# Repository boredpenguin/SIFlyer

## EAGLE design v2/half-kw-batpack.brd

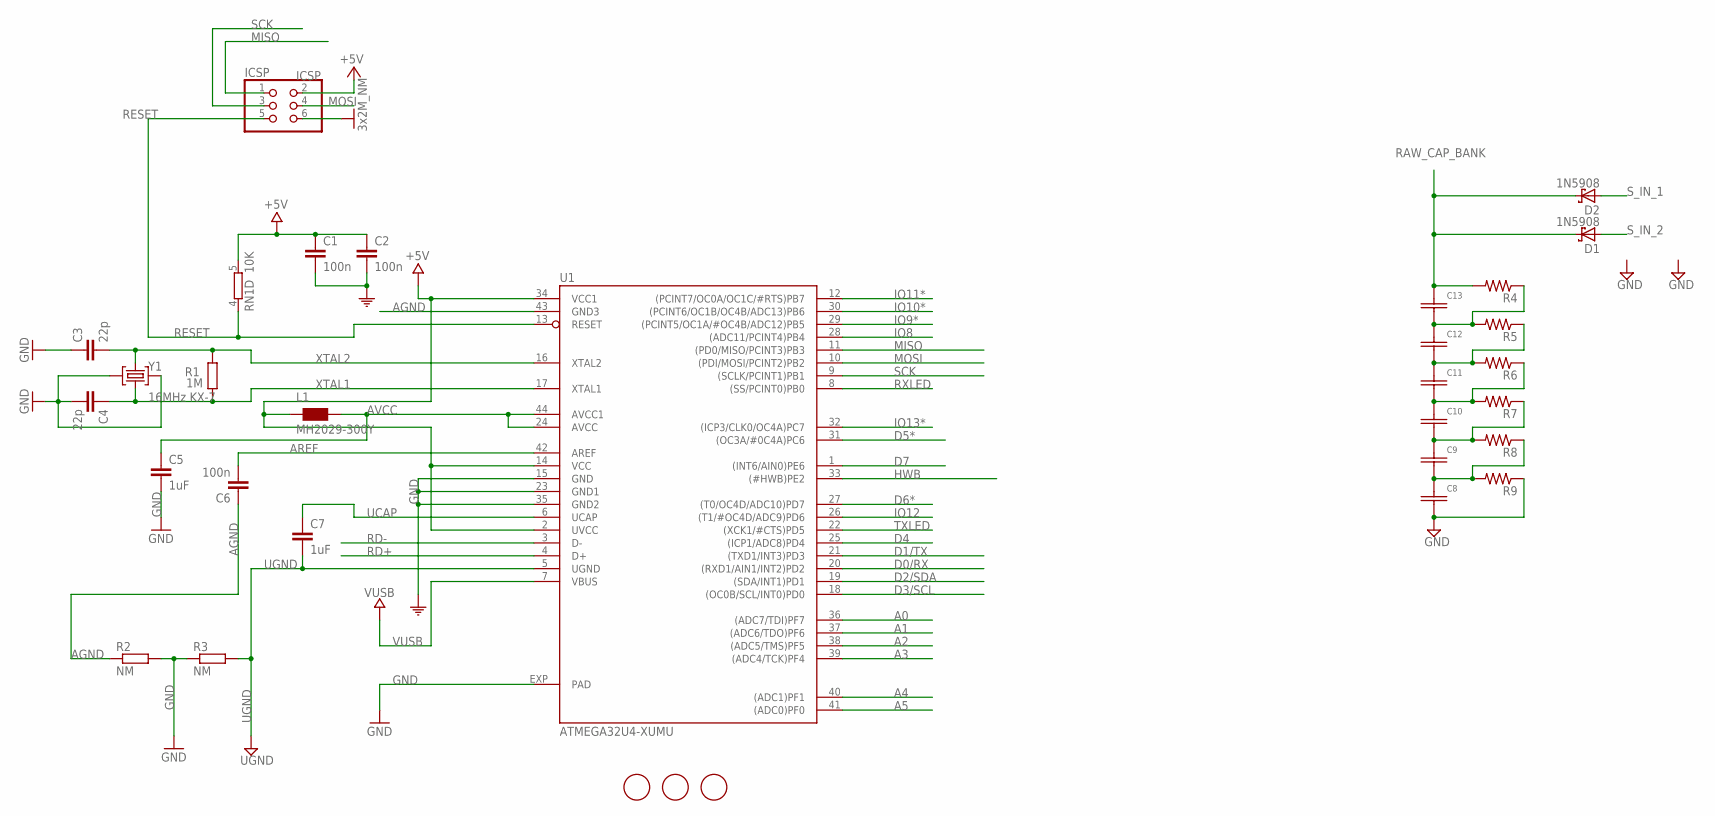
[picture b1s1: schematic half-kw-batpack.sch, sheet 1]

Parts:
C1, C2, C6: 100n; C0603-ROUND
C3, C4: 22p; C0603-ROUND
C5, C7: 1uF; C0603-ROUND
C8, C9, C10, C11, C12, C13: BCAP0100; MAXWELLBCAP100
D1, D2: 1N5908; C4111-15
FID1, FID2, FID3: FIDUCIALMOUNT; FIDUCIA-MOUNT
ICSP: ICSP; 2X03
L1: MH2029-300Y; 0805
R1: 1M; R0603-ROUND
R2, R3: NM; R0402
R4, R5, R6, R7, R8, R9: R-US_R1206; R1206
RN1: 10K; CAY16
U1: ATMEGA32U4-XUMU; QFN44ML7X7
Y1: 16MHz KX-7; CRYSTAL-3.2-2.5

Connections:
+5V: C1.1, C2.1, ICSP.2, L1.1, RN1.5 (2), U1.2 (UVCC), U1.14 (VCC), U1.34 (VCC1)
A0: U1.36 ((ADC7/TDI)PF7)
A1: U1.37 ((ADC6/TDO)PF6)
A2: U1.38 ((ADC5/TMS)PF5)
A3: U1.39 ((ADC4/TCK)PF4)
A4: U1.40 ((ADC1)PF1)
A5: U1.41 ((ADC0)PF0)
AGND: C6.1, R2.1, U1.43 (GND3)
AREF: C6.2, U1.42 (AREF)
AVCC: C5.1, L1.2, U1.24 (AVCC), U1.44 (AVCC1)
D0/RX: U1.20 ((RXD1/AIN1/INT2)PD2)
D1/TX: U1.21 ((TXD1/INT3)PD3)
D2/SDA: U1.19 ((SDA/INT1)PD1)
D3/SCL: U1.18 ((OC0B/SCL/INT0)PD0)
D4: U1.25 ((ICP1/ADC8)PD4)
D5*: U1.31 ((OC3A/#0C4A)PC6)
D6*: U1.27 ((T0/OC4D/ADC10)PD7)
D7: U1.1 ((INT6/AIN0)PE6)
GND: C1.2, C2.2, C3.1, C4.2, C5.2, C8.P$2, ICSP.6, R2.2, R3.1, R9.1, U1.15 (GND), U1.23 (GND1), U1.35 (GND2), U1.EXP (PAD), Y1.2 (GND), Y1.4 (GND)
HWB: U1.33 ((#HWB)PE2)
IO8: U1.28 ((ADC11/PCINT4)PB4)
IO9*: U1.29 ((PCINT5/OC1A/#OC4B/ADC12)PB5)
IO10*: U1.30 ((PCINT6/OC1B/OC4B/ADC13)PB6)
IO11*: U1.12 ((PCINT7/OC0A/OC1C/#RTS)PB7)
IO12: U1.26 ((T1/#OC4D/ADC9)PD6)
IO13*: U1.32 ((ICP3/CLK0/OC4A)PC7)
MISO: ICSP.1, U1.11 ((PD0/MISO/PCINT3)PB3)
MOSI: ICSP.4, U1.10 ((PDI/MOSI/PCINT2)PB2)
unnamed: C9.P$1, C10.P$2, R7.1, R8.2
unnamed: C10.P$1, C11.P$2, R6.1, R7.2
unnamed: C12.P$1, C13.P$2, R4.1, R5.2
unnamed: C11.P$1, C12.P$2, R5.1, R6.2
unnamed: C8.P$1, C9.P$2, R8.1, R9.2
RAW_CAP_BANK: C13.P$1, D1.C, D2.C, R4.2
RD+: U1.4 (D+)
RD-: U1.3 (D-)
RESET: ICSP.5, RN1.4 (1), U1.13 (RESET)
RXLED: U1.8 ((SS/PCINT0)PB0)
SCK: ICSP.3, U1.9 ((SCLK/PCINT1)PB1)
S_IN_1: D2.A
S_IN_2: D1.A
TXLED: U1.22 ((XCK1/#CTS)PD5)
UCAP: C7.1, U1.6 (UCAP)
UGND: C7.2, R3.2, U1.5 (UGND)
VUSB: U1.7 (VBUS)
XTAL1: C4.1, R1.1, U1.17 (XTAL1), Y1.1 (C1)
XTAL2: C3.2, R1.2, U1.16 (XTAL2), Y1.3 (C2)

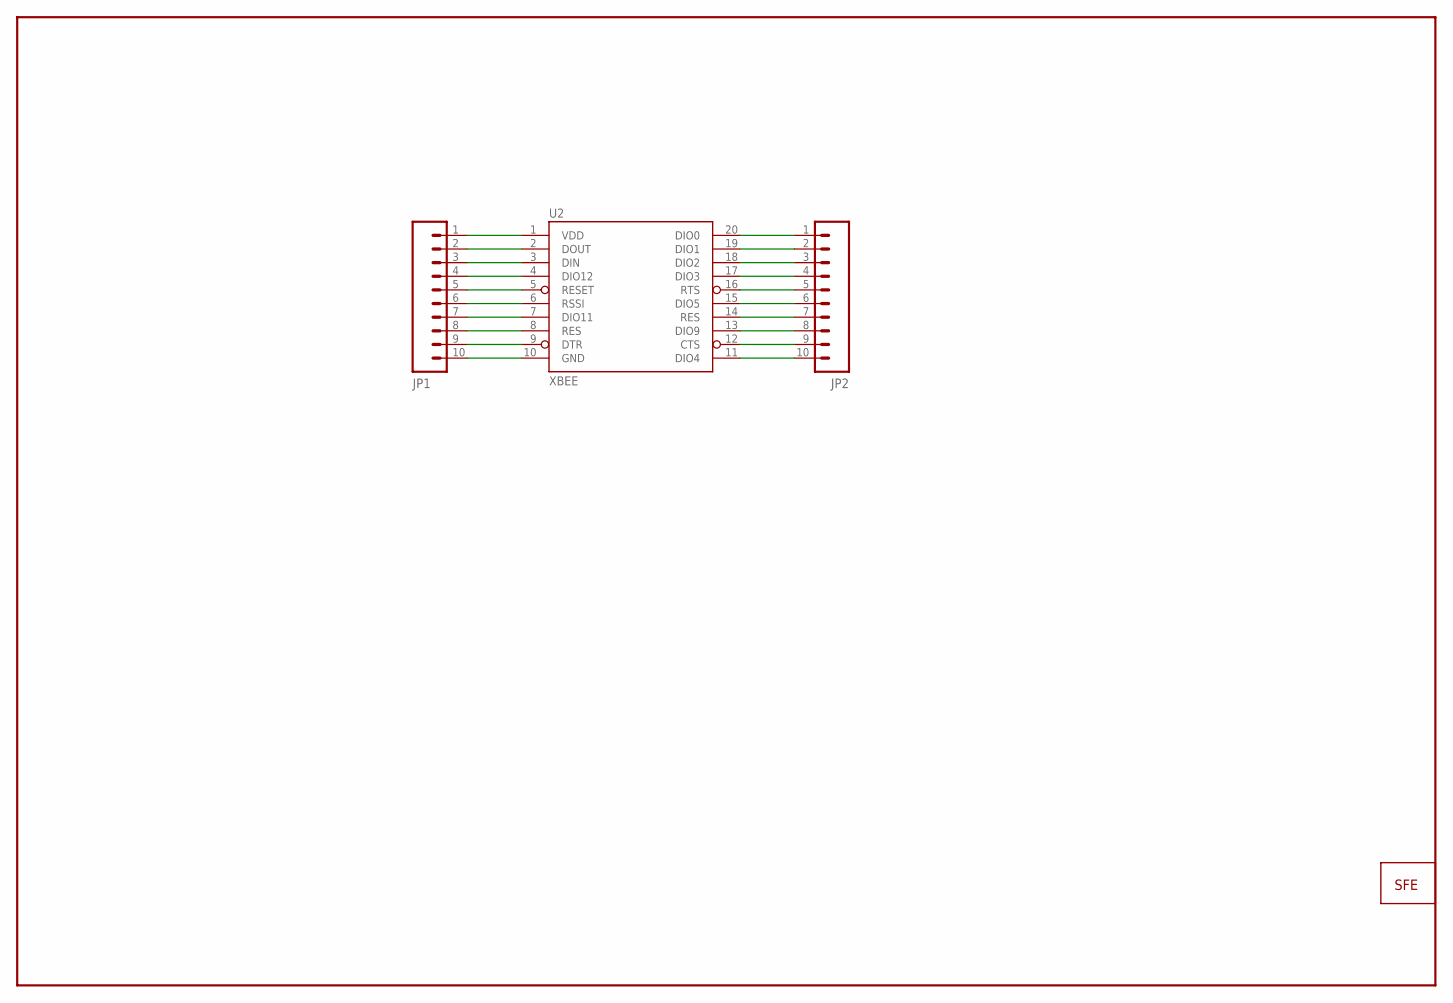
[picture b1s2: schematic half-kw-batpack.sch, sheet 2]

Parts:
JP1, JP2: M100.1; 1X10
U2: XBEE; XBEE-1
U$2: LOGO-SFENEW; SFE-NEW-WEBLOGO

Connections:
unnamed: JP1.5, U2.5 (RESET)
unnamed: JP1.1, U2.1 (VDD)
unnamed: JP1.2, U2.2 (DOUT)
unnamed: JP1.3, U2.3 (DIN)
unnamed: JP1.4, U2.4 (DIO12)
unnamed: JP1.6, U2.6 (RSSI)
unnamed: JP1.7, U2.7 (DIO11)
unnamed: JP1.8, U2.8 (RES)
unnamed: JP1.9, U2.9 (DTR)
unnamed: JP1.10, U2.10 (GND)
unnamed: JP2.10, U2.11 (DIO4)
unnamed: JP2.9, U2.12 (CTS)
unnamed: JP2.8, U2.13 (DIO9)
unnamed: JP2.7, U2.14 (RES)
unnamed: JP2.6, U2.15 (DIO5)
unnamed: JP2.5, U2.16 (RTS)
unnamed: JP2.4, U2.17 (DIO3)
unnamed: JP2.3, U2.18 (DIO2)
unnamed: JP2.2, U2.19 (DIO1)
unnamed: JP2.1, U2.20 (DIO0)

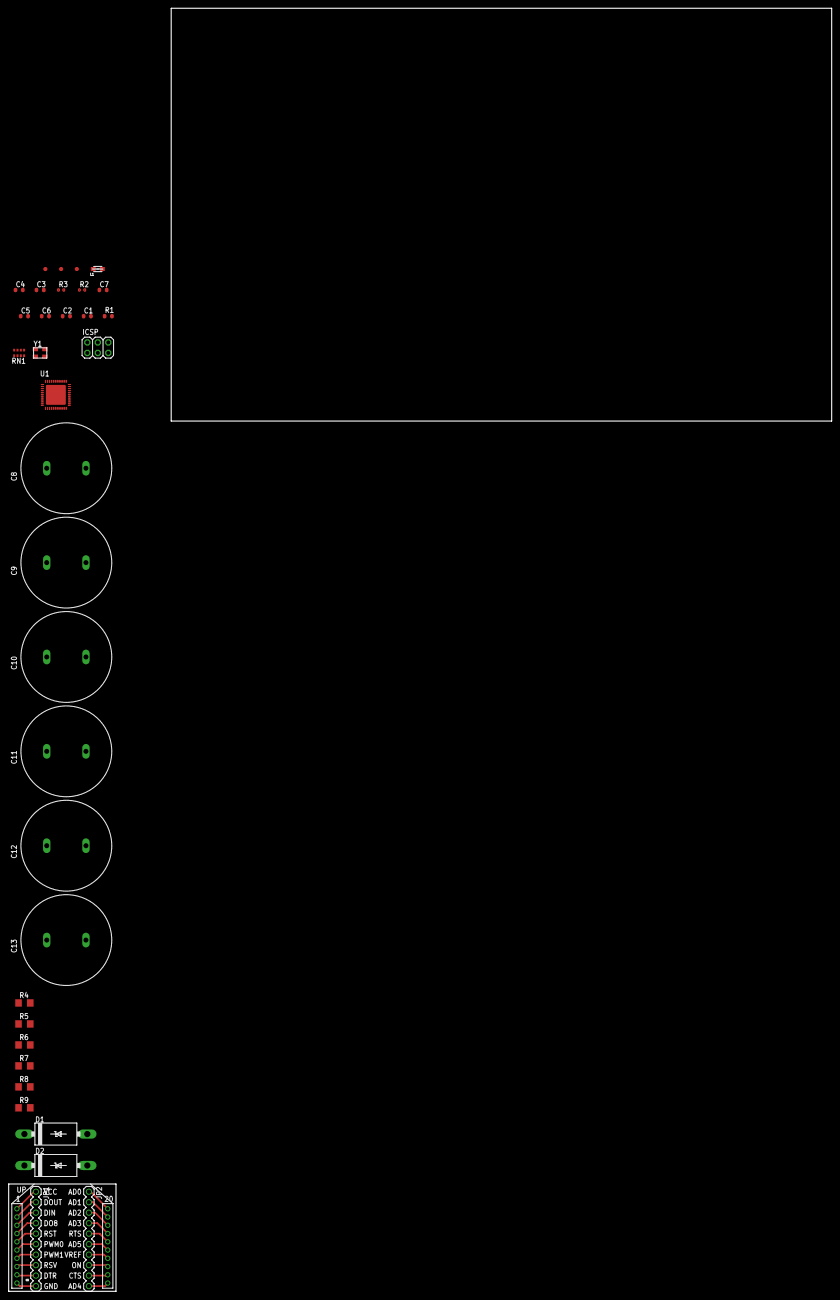
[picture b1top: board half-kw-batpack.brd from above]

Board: 2 copper layers, 36 parts (1 on the bottom side), 39 nets.

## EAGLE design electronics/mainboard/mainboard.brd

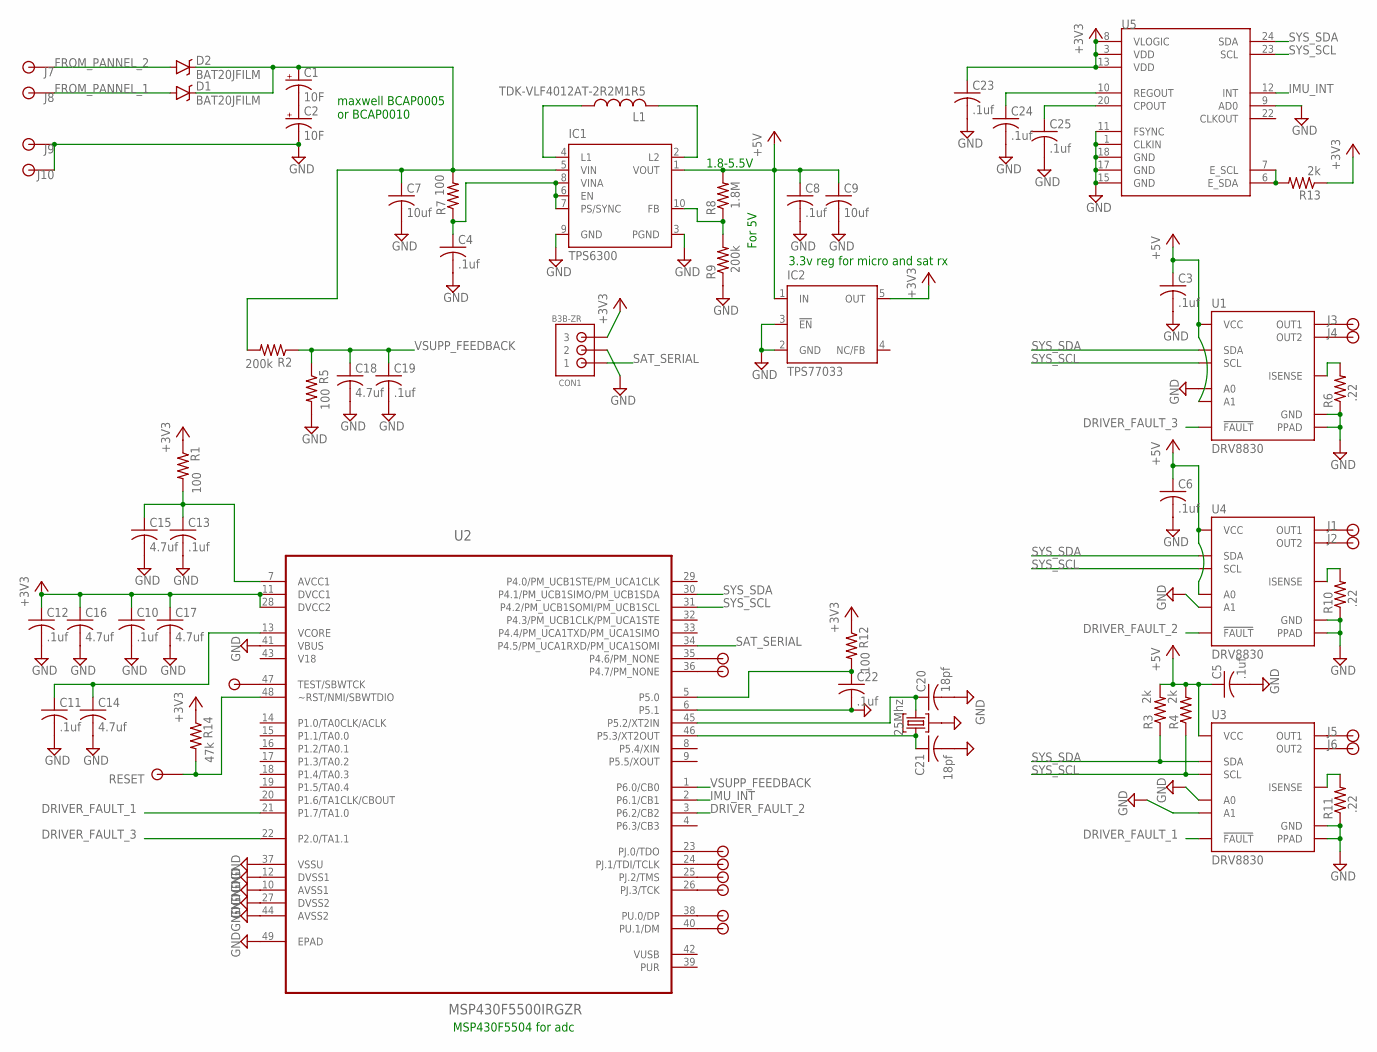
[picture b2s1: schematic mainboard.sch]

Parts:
C1, C2: 10F; E5-10,5
C3, C4, C5, C6, C8, C10, C11, C12, C13, C19, C22, C23, C24, C25: .1uf; C0603
C7, C9: 10uf; C0603
C14, C15, C16, C17, C18: 4.7uf; C0603
C20, C21: 18pf; C0603
CON1: B3B-ZR
D1, D2: BAT20JFILM; SOD-323
IC1: TPS6300; DRC-S-PVSON-N10
IC2: TPS77033; SOT23-DBV
J1, J2, J3, J4, J5, J6, J7, J8, J9, J10: 2MMPAD
J11, J12, J13, J14, J15, J16, J17, J18, J19, J20: ROUND1MM
L1: TDK-VLF4012AT-2R2M1R5
Q1: 25Mhz; SMD-3.2X2.5
R1, R5, R7, R12: 100; R0402
R2, R9: 200k; R0402
R3, R4, R13: 2k; R0402
R6, R10, R11: .22; R0402
R8: 1.8M; R0402
R14: 47k; R0402
U1, U3, U4: DRV8830; MSOP-10-GNDPAD
U2: MSP430F5500IRGZR; QFN50P700X700X100-49N
U5: MPU-9150QFN-24-NP; QFN-24-NP

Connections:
+3V3: C10.1, C12.1, C16.1, C17.1, C23.1, CON1.3, IC2.5 (OUT), R1.1, R12.1, R13.1, R14.1, U2.11 (DVCC1), U2.28 (DVCC2), U5.3 (VDD), U5.8 (VLOGIC), U5.13 (VDD)
+5V: C3.1, C5.1, C6.1, C8.1, C9.1, IC1.1 (VOUT), IC2.1 (IN), R3.2, R4.2, R8.2, U1.4 (VCC), U1.8 (A1), U3.4 (VCC), U4.4 (VCC), U4.7 (A0)
DRIVER_FAULT_1: U2.21 (P1.7/TA1.0), U3.6 (!FAULT)
DRIVER_FAULT_2: U2.3 (P6.2/CB2), U4.6 (!FAULT)
DRIVER_FAULT_3: U1.6 (!FAULT), U2.22 (P2.0/TA1.1)
FROM_PANNEL_1: D1.A, J8.P$1
FROM_PANNEL_2: D2.A, J7.P$1
GND: C2.-, C3.2, C4.2, C5.2, C6.2, C7.2, C8.2, C9.2, C10.2, C11.2, C12.2, C13.2, C14.2, C15.2, C16.2, C17.2, C18.2, C19.2, C20.2, C21.2, C22.2, C23.2, C24.2, C25.2, CON1.2, IC1.3 (PGND), IC1.9 (GND), IC2.2 (GND), IC2.3 (!EN), J9.P$1, J10.P$1, Q1.P$2 (2), Q1.P$4 (2), R5.2, R6.1, R9.1, R10.1, R11.1, U1.5 (GND), U1.7 (A0), U1.GND (PPAD), U2.6 (P5.1), U2.10 (AVSS1), U2.12 (DVSS1), U2.27 (DVSS2), U2.37 (VSSU), U2.41 (VBUS), U2.44 (AVSS2), U2.49 (EPAD), U3.5 (GND), U3.7 (A0), U3.8 (A1), U3.GND (PPAD), U4.5 (GND), U4.8 (A1), U4.GND (PPAD), U5.1 (CLKIN), U5.9 (AD0), U5.11 (FSYNC), U5.15 (GND), U5.17 (GND), U5.18 (GND)
IMU_INT: U2.2 (P6.1/CB1), U5.12 (INT)
unnamed: C1.-, C2.+
unnamed: C1.+, C7.1, D1.C, D2.C, IC1.5 (VIN), R2.2, R7.2
unnamed: IC1.4 (L1), L1.P$1 (1)
unnamed: IC1.2 (L2), L1.P$2 (2)
unnamed: C13.1, C15.1, R1.2, U2.7 (AVCC1)
unnamed: J1.P$1, U4.3 (OUT1)
unnamed: C11.1, C14.1, U2.13 (VCORE)
unnamed: C4.1, IC1.6 (EN), IC1.7 (PS/SYNC), IC1.8 (VINA), R7.1
unnamed: IC1.10 (FB), R8.1, R9.2
unnamed: J2.P$1, U4.1 (OUT2)
unnamed: J3.P$1, U1.3 (OUT1)
unnamed: J4.P$1, U1.1 (OUT2)
unnamed: J5.P$1, U3.3 (OUT1)
unnamed: J6.P$1, U3.1 (OUT2)
unnamed: C20.1, Q1.P$1 (3), U2.45 (P5.2/XT2IN)
unnamed: C21.1, Q1.P$3 (1), U2.46 (P5.3/XT2OUT)
unnamed: R6.2, U1.2 (ISENSE)
unnamed: R11.2, U3.2 (ISENSE)
unnamed: R10.2, U4.2 (ISENSE)
unnamed: C22.1, R12.2, U2.5 (P5.0)
unnamed: R13.2, U5.6 (E_SDA), U5.7 (E_SCL)
unnamed: C24.1, U5.10 (REGOUT)
unnamed: C25.1, U5.20 (CPOUT)
unnamed: J11.P$1, U2.23 (PJ.0/TDO)
unnamed: J12.P$1, U2.24 (PJ.1/TDI/TCLK)
unnamed: J13.P$1, U2.25 (PJ.2/TMS)
unnamed: J14.P$1, U2.26 (PJ.3/TCK)
unnamed: J16.P$1, U2.47 (TEST/SBWTCK)
unnamed: J17.P$1, U2.36 (P4.7/PM_NONE)
unnamed: J18.P$1, U2.35 (P4.6/PM_NONE)
unnamed: J19.P$1, U2.38 (PU.0/DP)
unnamed: J20.P$1, U2.40 (PU.1/DM)
RESET: J15.P$1, R14.2, U2.48 (~RST/NMI/SBWTDIO)
SAT_SERIAL: CON1.1, U2.34 (P4.5/PM_UCA1RXD/PM_UCA1SOMI)
SYS_SCL: R4.1, U1.10 (SCL), U2.31 (P4.2/PM_UCB1SOMI/PM_UCB1SCL), U3.10 (SCL), U4.10 (SCL), U5.23 (SCL)
SYS_SDA: R3.1, U1.9 (SDA), U2.30 (P4.1/PM_UCB1SIMO/PM_UCB1SDA), U3.9 (SDA), U4.9 (SDA), U5.24 (SDA)
V18: U2.43 (V18)
VSUPP_FEEDBACK: C18.1, C19.1, R2.1, R5.1, U2.1 (P6.0/CB0)

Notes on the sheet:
maxwell BCAP0005 or BCAP0010
1.8-5.5V
3.3v reg for micro and sat rx
For 5V
MSP430F5504 for adc

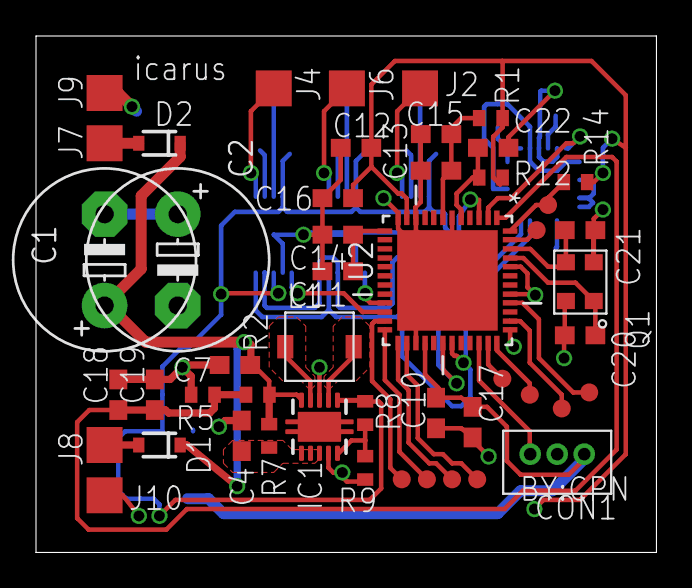
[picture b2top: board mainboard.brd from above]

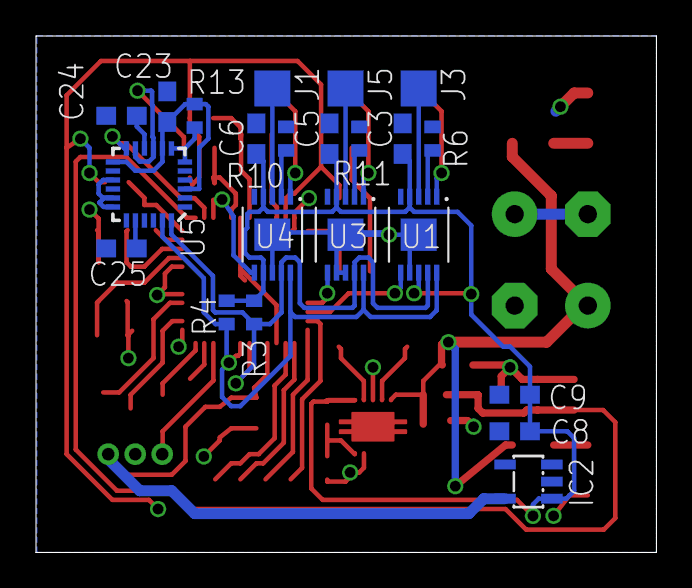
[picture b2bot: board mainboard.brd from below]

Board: 2 copper layers, 34.5 x 28.7 mm, 71 parts (22 on the bottom side), 46 nets.

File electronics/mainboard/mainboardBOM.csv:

link	Qty	Value	Device	Package	Parts	Description	MF	MFG	MFN	MPN	OC_FARNELL	OC_NEWARK	PACKAGE	PROD_ID	SUPPLIER	VALUE				
http://www.digikey.com/product-detail/en/MPU-9150/1428-1009-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	1		MPU-9150QFN-24-NP	QFN-24-NP	U5	9DOF (3mag	 3accel	 3rotat). I2C interface.												
http://www.digikey.com/product-detail/en/GRM188R71C104KA01D/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	14	.1uf	C-USC0603	C0603	C3	 C4	 C5	 C6	 C8	 C10	 C11	 C12	 C13	 C19	 C22	 C23	 C24	 C25	CAPACITOR	 American symbol
http://www.digikey.com/product-detail/en/RU1608FR022CS/1276-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	3	0.22	R-US_R0402	R0402	R6	 R10	 R11	RESISTOR	 American symbol											
http://www.digikey.com/product-detail/en/ERJ-2GEJ185X/P1.8MJ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	1	1.8M	R-US_R0402	R0402	R8	RESISTOR	 American symbol													
http://www.digikey.com/product-detail/en/RMCF0402JT100R/RMCF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	4	100	R-US_R0402	R0402	R1	 R5	 R7	 R12	RESISTOR	 American symbol										
	2	10F	CPOL-USE5-10.5	E5-10	5	C1	 C2	POLARIZED CAPACITOR	 American symbol											
http://www.digikey.com/product-detail/en/AMK107ABJ106MAHT/58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	2	10uf	C-USC0603	C0603	C7	 C9	CAPACITOR	 American symbol												
http://www.digikey.com/product-detail/en/C0603C180J5GACTU/39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	2	18pf	C-USC0603	C0603	C20	 C21	CAPACITOR	 American symbol												
http://www.digikey.com/product-detail/en/ERJ-2RKF2003X/P200K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	2	200k	R-US_R0402	R0402	R2	 R9	RESISTOR	 American symbol												
http://www.digikey.com/product-detail/en/403C35D25M00000/CTX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	1	25Mhz	CRYSTAL-GROUNDED	CRYSTAL-SMD-5X3	Q1															
	10	2MMPAD	2MMPAD	2MMPAD	J1	 J2	 J3	 J4	 J5	 J6	 J7	 J8	 J9	 J10						
http://www.digikey.com/product-detail/en/RMCF0402FT2K00/RMCF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	3	2k	R-US_R0402	R0402	R3	 R4	 R13	RESISTOR	 American symbol											
http://www.digikey.com/product-detail/en/F981C475MMA/478-865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	5	4.7uf	C-USC0603	C0603	C14	 C15	 C16	 C17	 C18	CAPACITOR	 American symbol									
http://www.digikey.com/product-detail/en/RMCF0402FT47K0/RMCF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	1	47k	R-US_R0402	R0402	R14	RESISTOR	 American symbol													
	1	B3B-ZR	B3B-ZR	B3B-ZR	CON1	JST-ZH Connector														
http://www.digikey.com/product-detail/en/BAT20JFILM/497-3381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	2	BAT20JFILM	BAT20JFILM	SOD-323	D1	 D2	23V	 1A Schottky diode	 SOD-323 package								DIO-11623		BAT20JFILM	
http://www.digikey.com/product-detail/en/DRV8830DGQR/296-281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	3	DRV8830	DRV8830	MSOP-10-GNDPAD	U1	 U3	 U4	DRV8830 I2C DC Motor Driver								IC-11646				
http://www.mouser.com/ProductDetail/Texas-Instruments/MSP430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	1	MSP430F5500IRGZR	MSP430F5500IRGZR	QFN50P700X700X100-49N	U2	MIXED SIGNAL MICROCONTROLLER				MSP430F5500IRGZR	1972383	27T6606	VQFN-48		TEXAS INSTRUMENTS					
	6	ROUND1MM	ROUND1MM	ROUND1MM	J11	 J12	 J13	 J14	 J15	 J16										
http://www.digikey.com/product-detail/en/VLF4012AT-2R2M1R5/4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	1	TDK-VLF4012AT-2R2M1R5	TDK-VLF4012AT-2R2M1R5	TDK-VLF4012AT-2R2M1R5	L1			TDK	VLF4012AT-2R2M1R5											
http://www.digikey.com/product-detail/en/TPS63000DRCR/296-19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	1	TPS6300	TPS6300	DRC-S-PVSON-N10	IC1	HIGH EFFICIENT SINGLE INDUCTOR BUCK-BOOST CONVERTER WITH 1.8-A SWITCHES				TPS63000DRCTG4	1511852	59M7217								
http://www.digikey.com/product-detail/en/TPS77033DBVR/296-11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	1	TPS77033	TPS77033	SOT23-DBV	IC2	ULTRALOW-POWER 50-mA LOW-DROPOUT LINEAR REGULATORS	TEXAS INSTRUMENTS			TPS77033DBVT	8461570	77C1187

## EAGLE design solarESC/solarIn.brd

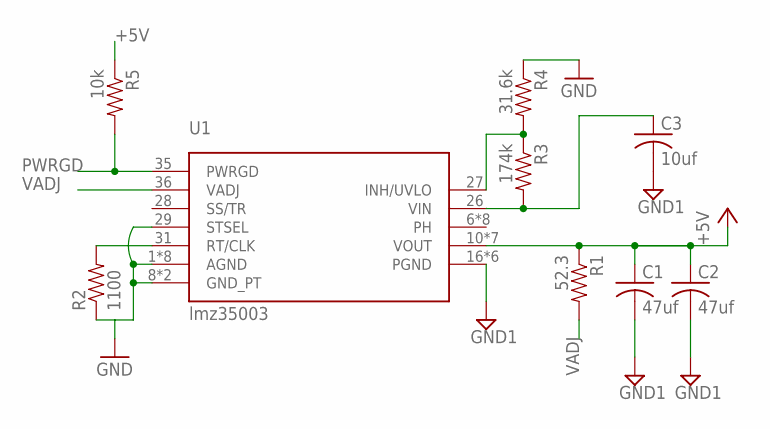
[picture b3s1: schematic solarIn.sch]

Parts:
C1, C2: 47uf; C0805
C3: 10uf; C0805
R1: 52.3; 0603-RES
R2: 1100; 0603-RES
R3: 174k; 0603-RES
R4: 31.6k; 0603-RES
R5: 10k; 0603-RES
U1: LMZ35003; S-PB1QFN-N41

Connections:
+5V: R5.1
GND: R2.1, R4.1, U1.1 (AGND), U1.4 (AGND), U1.5 (AGND), U1.8 (GND_PT), U1.9 (GND_PT), U1.29 (STSEL), U1.30 (AGND), U1.32 (AGND), U1.33 (AGND), U1.34 (AGND), U1.37 (AGND)
GND1: C1.2, C2.2, C3.2, U1.16 (PGND), U1.17 (PGND), U1.18 (PGND), U1.19 (PGND), U1.20 (PGND), U1.40 (PGND)
unnamed: R2.2, U1.31 (RT/CLK)
unnamed: R3.1, R4.2, U1.27 (INH/UVLO)
PWRGD: R5.2, U1.35 (PWRGD)
VADJ: R1.2, U1.36 (VADJ)
VIN: C3.1, R3.2, U1.26 (VIN)
VOUT: C1.1, C2.1, R1.1, U1.10 (VOUT), U1.11 (VOUT), U1.12 (VOUT), U1.13 (VOUT), U1.14 (VOUT), U1.15 (VOUT), U1.39 (VOUT)

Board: 2 copper layers, 9 parts (0 on the bottom side), 8 nets, no tracks yet.

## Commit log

2014-06-26 init, started power layout
2014-06-27 added msp430, went with drv ti motor drivers for galvos and brushed motor, max 1.8A
2014-06-30 added passives to dc/dc. todo figure out analog/micro stuff and connection points for motors
2014-06-30 forgot new lib
2014-07-01 added decoupling to mcu
2014-07-04 arraning components for layout. May move to 402 passives if it gets too crowded.
2014-07-07 added single chip imu, need to hooking up. Investigate i2c compatablity
2014-07-08 worked on imu layout/sch.
2014-07-10 continuing work on layout
2014-07-16 renamed some files and cleaned up. Added motordriver component
2014-07-16 layout mostly done, need to add programming header
2014-07-17 prelim finished board
2014-07-24 changed crystal. name change. minor tweaks
2014-07-24 minor changes for board production. REV0 off to board house
2014-10-25 started work on solar in for new ESC
2015-01-09 started work on larger v2

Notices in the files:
parts and their libraries:
SparkFun-DiscreteSemi: Licensing: Creative Commons ShareAlike 4.0 International - https://creativecommons.org/licenses/by-sa/4.0
